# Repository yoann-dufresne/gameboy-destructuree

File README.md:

# Game Boy Pocket déstructurée

Un projet artistique : éclater une Game Boy Pocket en objets indépendants qui se parlent
par WiFi.

Chaque module est un projet à part entière : il a son matériel, son firmware, sa
documentation, et il sert à quelque chose en dehors de la Game Boy.

## Modules

| Module | Ce qu'il fait |
|---|---|
| [`capture/`](capture/) | Espionne le bus LCD d'une vraie Game Boy Pocket et diffuse son image en UDP, sans perturber la console. |
| [`ecran/`](ecran/) | Afficheur réseau sur matrices LED, 192×192 pixels visés. Il affiche toute image qu'on lui envoie en UDP, quelle qu'en soit la source. |
| [`son/`](son/) | Prend le son d'une Game Boy Pocket avant son bouton de volume et le diffuse en UDP ; un haut-parleur réseau le joue. Phase 0 prête : banc de mesure, plan, tests et points de prise. |
| [`manette/`](manette/) | Une seconde Game Boy Pocket devenue manette WiFi : ses boutons, ses molettes et son interrupteur partent en UDP vers la console principale, où un injecteur appuie sur les boutons et l'allume ou l'éteint. Plan écrit, rien de construit. |
| [`cartouche/`](cartouche/) | La cartouche dans une fente à part : un lecteur la lit à l'insertion et en envoie la copie en WiFi à une doublure branchée sur la console principale, qui tient le rôle de la cartouche. Les sauvegardes reviennent à la vraie cartouche. Plan écrit, rien de construit. |

Les modules ne partagent que des protocoles réseau sur UDP : `PXL1` pour l'image ; `SON1`
pour le son, `MAN1` pour la manette et `CAR1` pour la cartouche, proposés. Chacun s'éprouve
seul : `capture` avec un écran virtuel sur PC, `ecran` avec un émetteur de test, `son` avec un
haut-parleur virtuel et un émetteur de test, `manette` avec un récepteur et une fausse manette
sur PC, `cartouche` avec un PC qui lit le lecteur ou envoie une ROM à la doublure.

Sur la console, chaque module a son microcontrôleur, qui émet son propre réseau WiFi : jusqu'à
quatre écrans, haut-parleurs ou manettes s'y connectent en direct. Le plan d'ensemble est dans
[`reseau.md`](reseau.md).

## Installer les outils

[`installer.sh`](installer.sh) installe, sur Ubuntu ou Debian, ce que tous les modules demandent :
`arm-none-eabi-gcc`, CMake, Ninja, `g++` pour les tests sur PC, le pico-sdk 2.3.1 dans
`~/pico/pico-sdk`, picotool, les outils Python et `sigrok-cli`. Il se relance sans danger.

Sous WSL2, l'USB passe par `usbipd-win` côté Windows ; le script affiche à la fin les commandes
à y taper. Les `tools/flash.sh` des modules reconnaissent WSL2 : ils flashent par picotool si le
Pico est attaché à WSL, sinon par le lecteur `RP2350` que voit Windows.

## Documents de conception

| Document | Contenu |
|---|---|
| [`reseau.md`](reseau.md) | Le réseau : un réseau par type de périphérique, émis par la console ; canaux, adresses, bus de la console, banc de coexistence. |
| [`banc-reseau/`](banc-reseau/) | Le banc de coexistence de `reseau.md` : firmwares et outil de verdict pour éprouver les quatre radios de la console, le sniffer en point d'accès et le bus de la console. |
| [`achats.md`](achats.md) | La liste d'achats du 11/10/2026, tous modules confondus, pour leurs prochaines phases et le banc de coexistence. |
| [`Spec_Gameboy_Pocket_Destructuree.md`](Spec_Gameboy_Pocket_Destructuree.md) | L'intention : une vraie console au centre, cinq modules, et ce qui a changé depuis la v1, qui plaçait un émulateur dans la cartouche. |
| [`Spec_Video_Sniffer_et_Matrice_LED.md`](Spec_Video_Sniffer_et_Matrice_LED.md) | Le départ de la chaîne vidéo : l'image prise sur une vraie console plutôt que sur un émulateur. |

La spécification principale dit l'intention d'aujourd'hui ; la spécification vidéo est le
document de départ de la chaîne image. Là où elles divergent de la documentation d'un module,
c'est le module qui fait foi : ses mesures les ont corrigées.

## Licence

Sauf mention contraire, ce dépôt est distribué sous licence
[GNU Affero General Public License v3.0 ou ultérieure](LICENSE) (AGPL-3.0-or-later).

Le contenu tiers garde sa licence d'origine :

- `ecran/firmware/vendor/hub75-jupfu/` : pilote HUB75 de JuPfu, licence MIT.
- Les fichiers `pico_sdk_import.cmake`, `lwipopts.h` et `ecran/firmware/phase0-bringup/hub75.pio`,
  repris ou dérivés du pico-sdk et de pico-examples de Raspberry Pi : licence BSD-3-Clause.
- `ecran/docs/seengreat-rgb-matrix-p3-64x64/` : documentation et codes de démonstration du
  fabricant Seengreat, archivés pour référence ; ils restent la propriété de leurs auteurs.

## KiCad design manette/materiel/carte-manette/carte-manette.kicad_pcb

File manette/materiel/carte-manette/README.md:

# La carte de la manette : les fichiers

Le plan, les décisions et les étapes sont dans [`../../docs/carte.md`](../../docs/carte.md). Ici, la
carte elle-même, régénérée par script, comme [celle de l'écran](../../../ecran/materiel/README.md) :
on ne retouche pas les fichiers KiCad à la main. On modifie `conception.py` ou `gen_pcb.py`, puis on
relance `construire.sh`. Les fichiers restent ouvrables dans KiCad 10 pour les regarder.

**État au 15/11/2026.**
- **Schéma complet (C1)** : le contrôle électrique ne trouve aucune erreur ni aucun avertissement,
  et la netlist de KiCad est identique à `conception.py`.
- **Géométrie posée (C2)** : le contour, les trous et les 11 pièces reprises de YAPoco sont à leur
  place exacte. Le Pico et la LED d'alimentation sont posés.
- **Les autres pièces attendent leur placement (C4)**, rangées hors de la feuille. Il dépend des
  relevés des membranes (C0) et de l'essai en carton (C3).

| Fichier | Rôle |
|---|---|
| `conception.py` | la description électrique : composants, empreintes, équipotentielles, références d'achat. Source unique |
| `gen_schema.py` | écrit `carte-manette.kicad_sch`, sa bibliothèque de symboles et les tables du projet |
| `gen_pcb.py` | écrit `carte-manette.kicad_pcb` : contour, trous, pièces placées. Vérifie chaque pastille reprise de YAPoco |
| `extrait_yapoco.py` | a tiré de YAPoco le contour, les empreintes et leur place. N'a pas à être relancé |
| `yapoco/` | ce qui vient de YAPoco, et sa provenance |
| `carte-manette.pretty/` | les empreintes propres à la carte |
| `kicadlib.py`, `verifie_netlist.py`, `bilan_drc.py` | outils repris de la carte de l'écran, adaptés à KiCad 10 |
| `construire.sh` | tout, du schéma au gabarit |
| `gabarit/gabarit-echelle-1.pdf` | le gabarit de l'essai en carton (C3) : la face avant, puis le dos vu de dos |

```bash
cd manette/materiel/carte-manette
./construire.sh
```

Prérequis : KiCad 10 (`kicad-cli` et le module Python `pcbnew`), Python 3, `pdfunite`. Les tables
du projet ne listent que les bibliothèques de la carte ; celles de KiCad viennent de ses tables
globales, les tables par défaut proposées au premier lancement.

**Imprimer le gabarit à 100 %, sans ajustement à la page** : le contour doit mesurer 69,5 × 114,4 mm
sur le papier.

## Licence

La carte reprend la géométrie de [YAPoco](https://github.com/nataliethenerd/YAPoco), de Natalie the
Nerd, publiée sous [CC BY-SA 4.0](https://creativecommons.org/licenses/by-sa/4.0/). Ce dossier est
publié sous la même licence ; le détail de ce qui est repris est dans
[`yapoco/PROVENANCE.txt`](yapoco/PROVENANCE.txt).

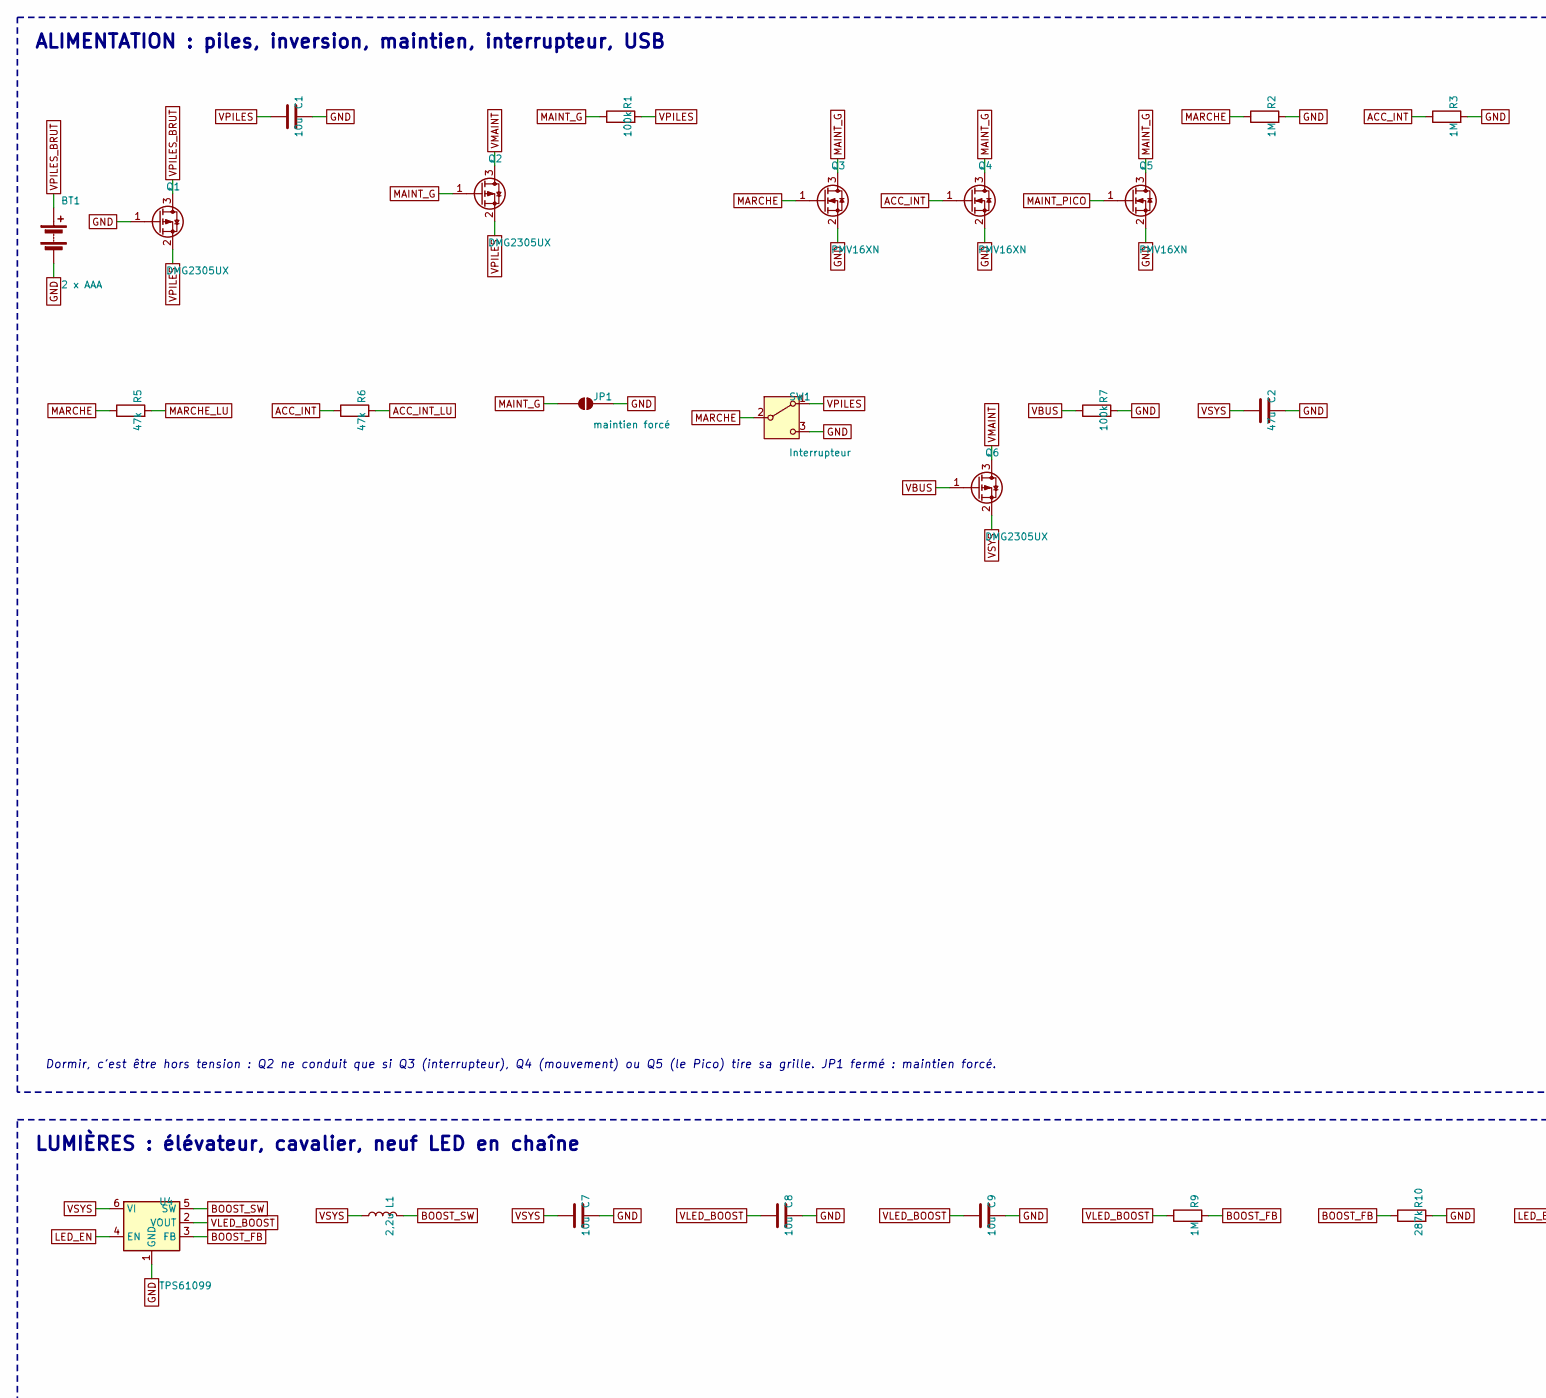
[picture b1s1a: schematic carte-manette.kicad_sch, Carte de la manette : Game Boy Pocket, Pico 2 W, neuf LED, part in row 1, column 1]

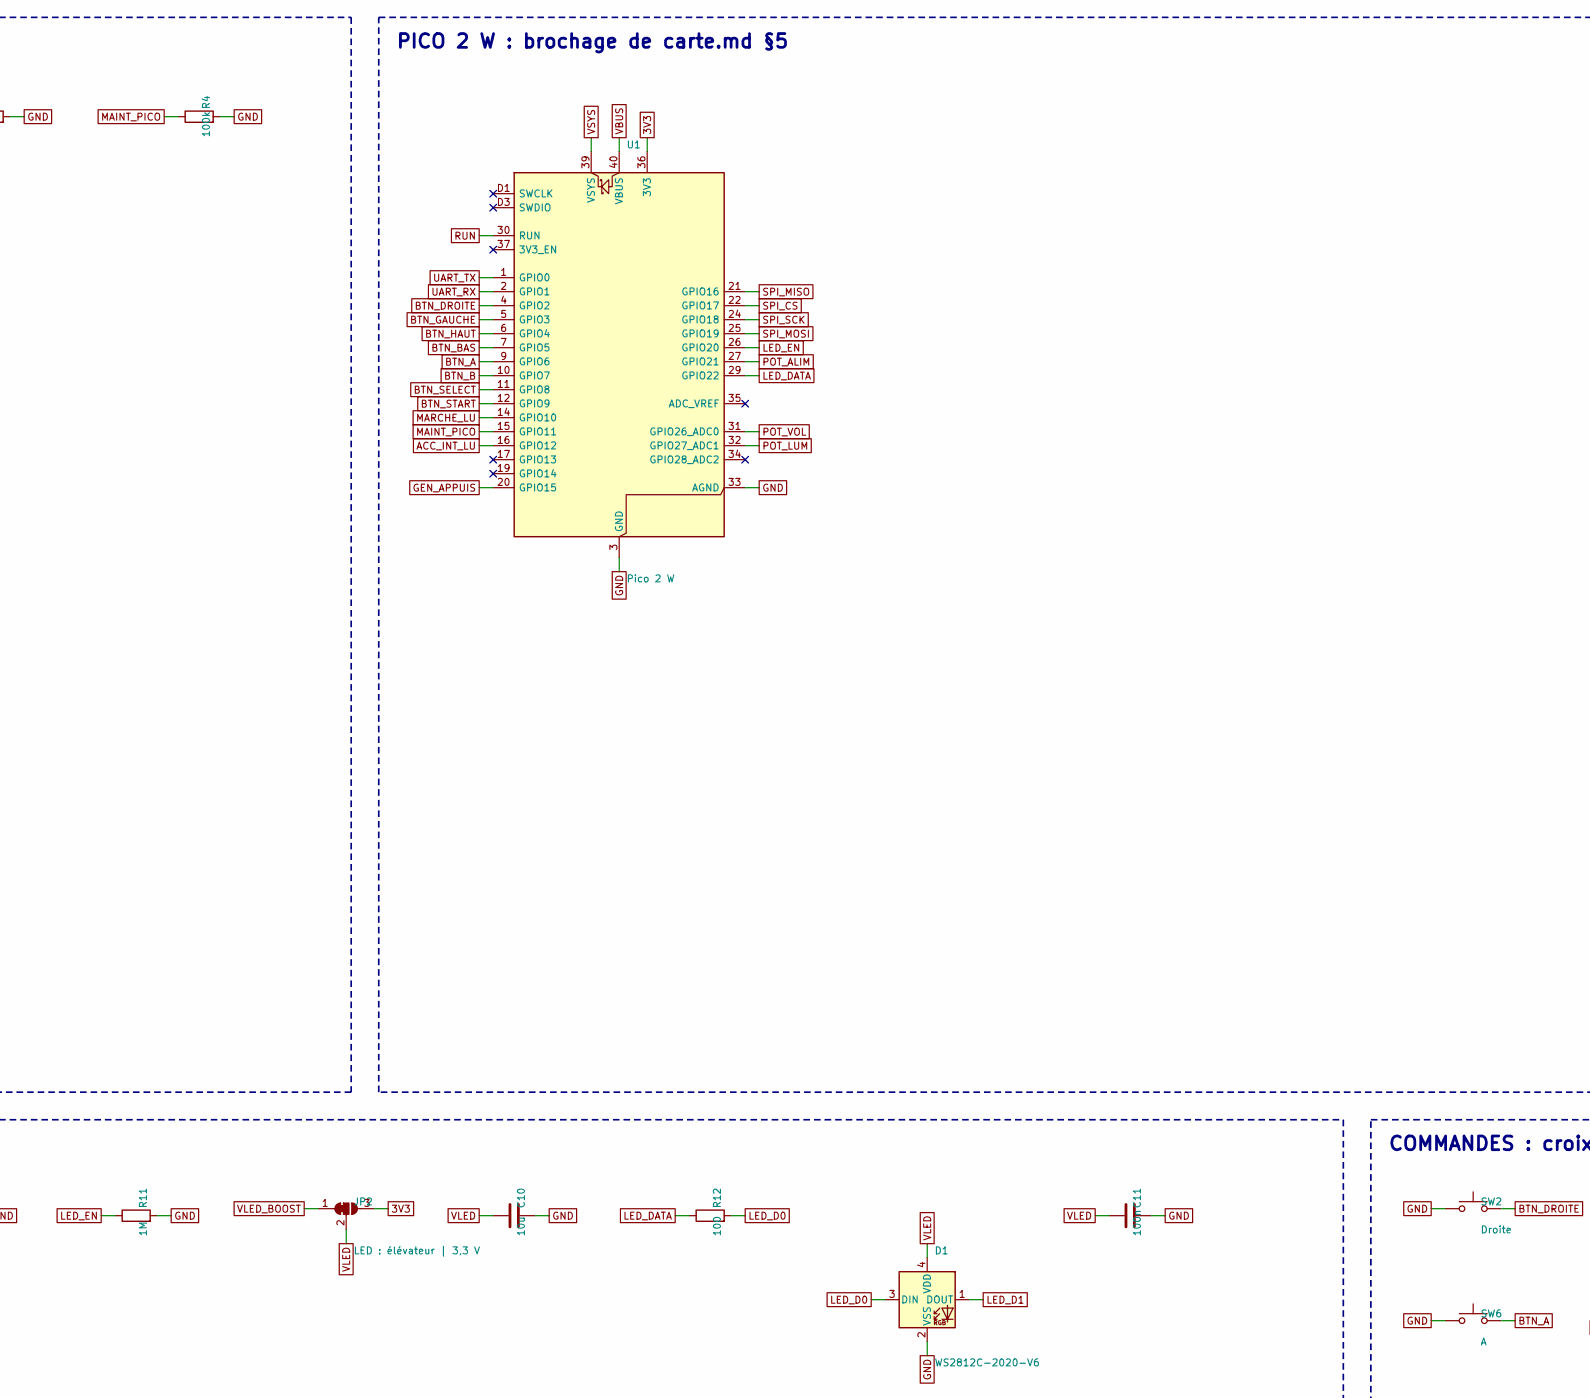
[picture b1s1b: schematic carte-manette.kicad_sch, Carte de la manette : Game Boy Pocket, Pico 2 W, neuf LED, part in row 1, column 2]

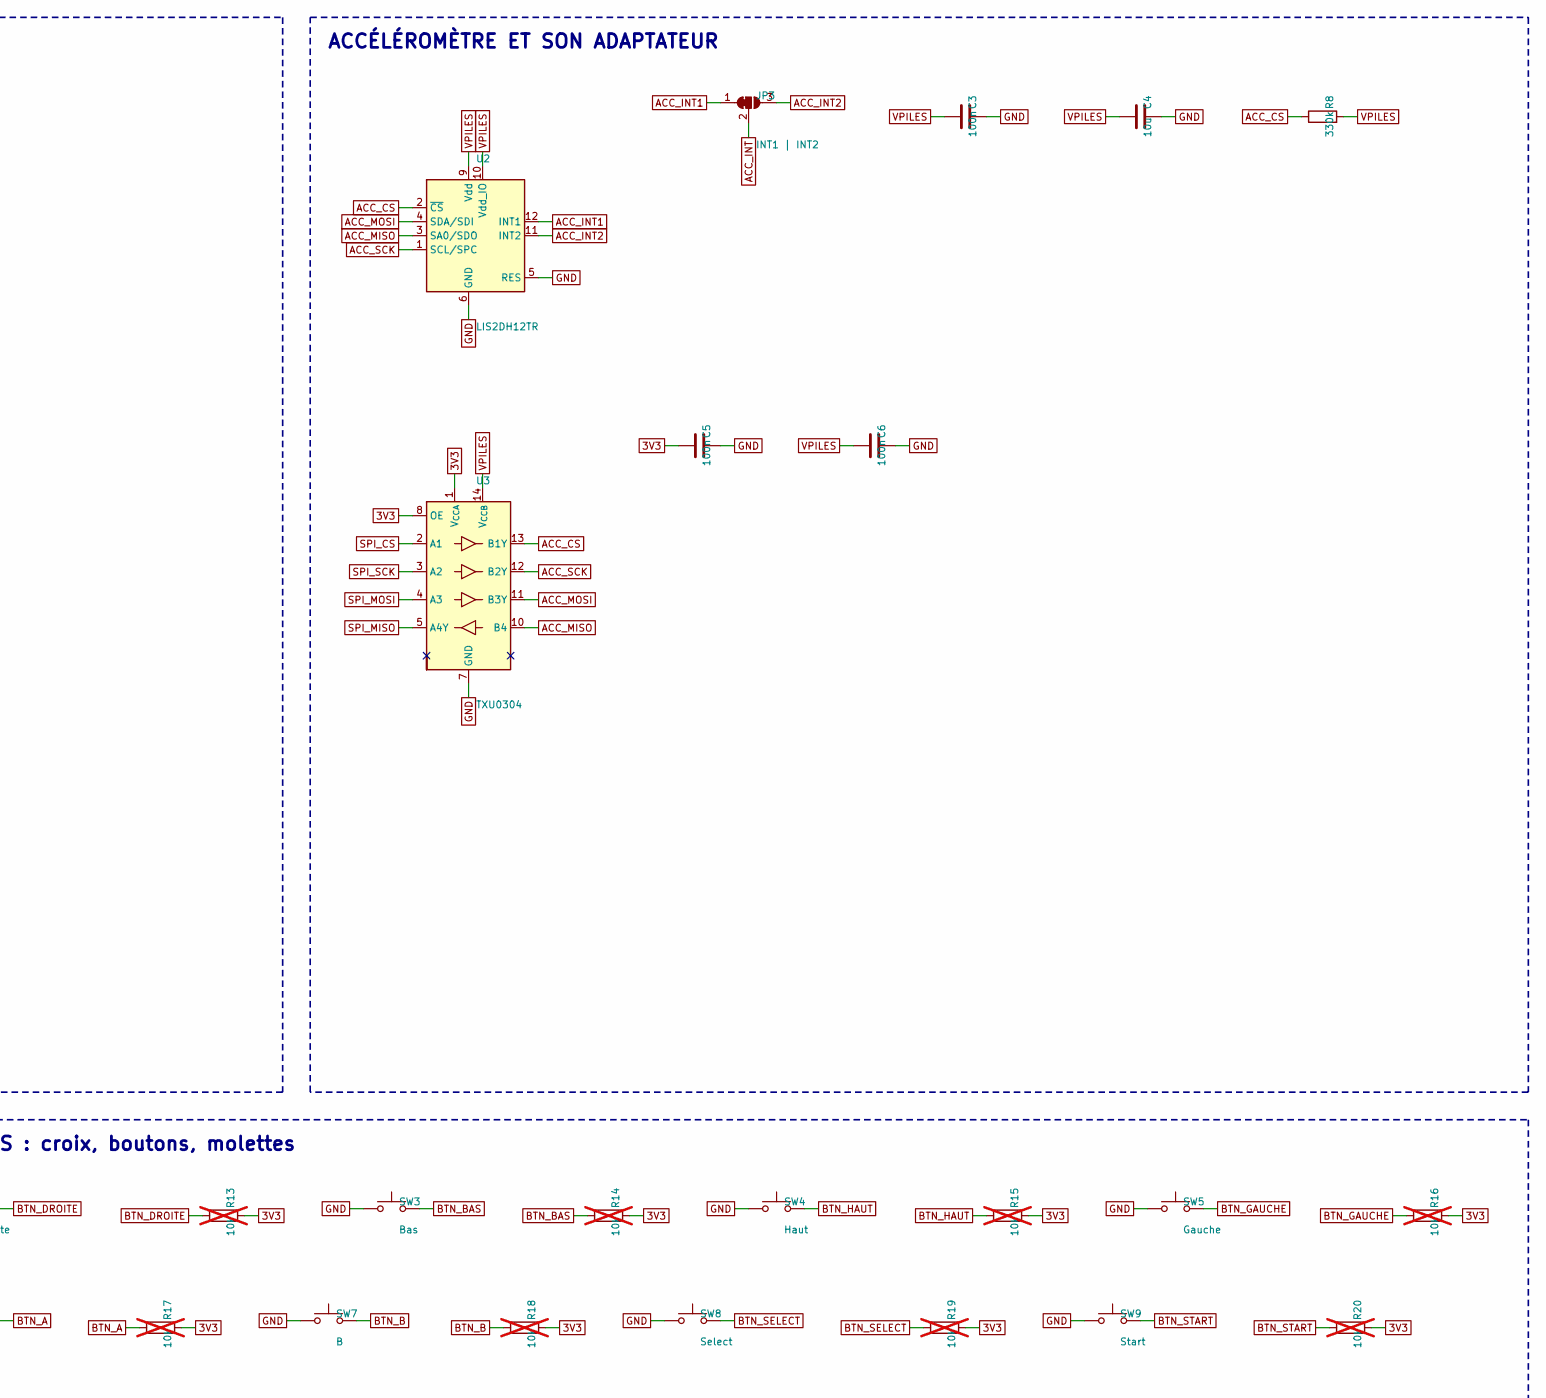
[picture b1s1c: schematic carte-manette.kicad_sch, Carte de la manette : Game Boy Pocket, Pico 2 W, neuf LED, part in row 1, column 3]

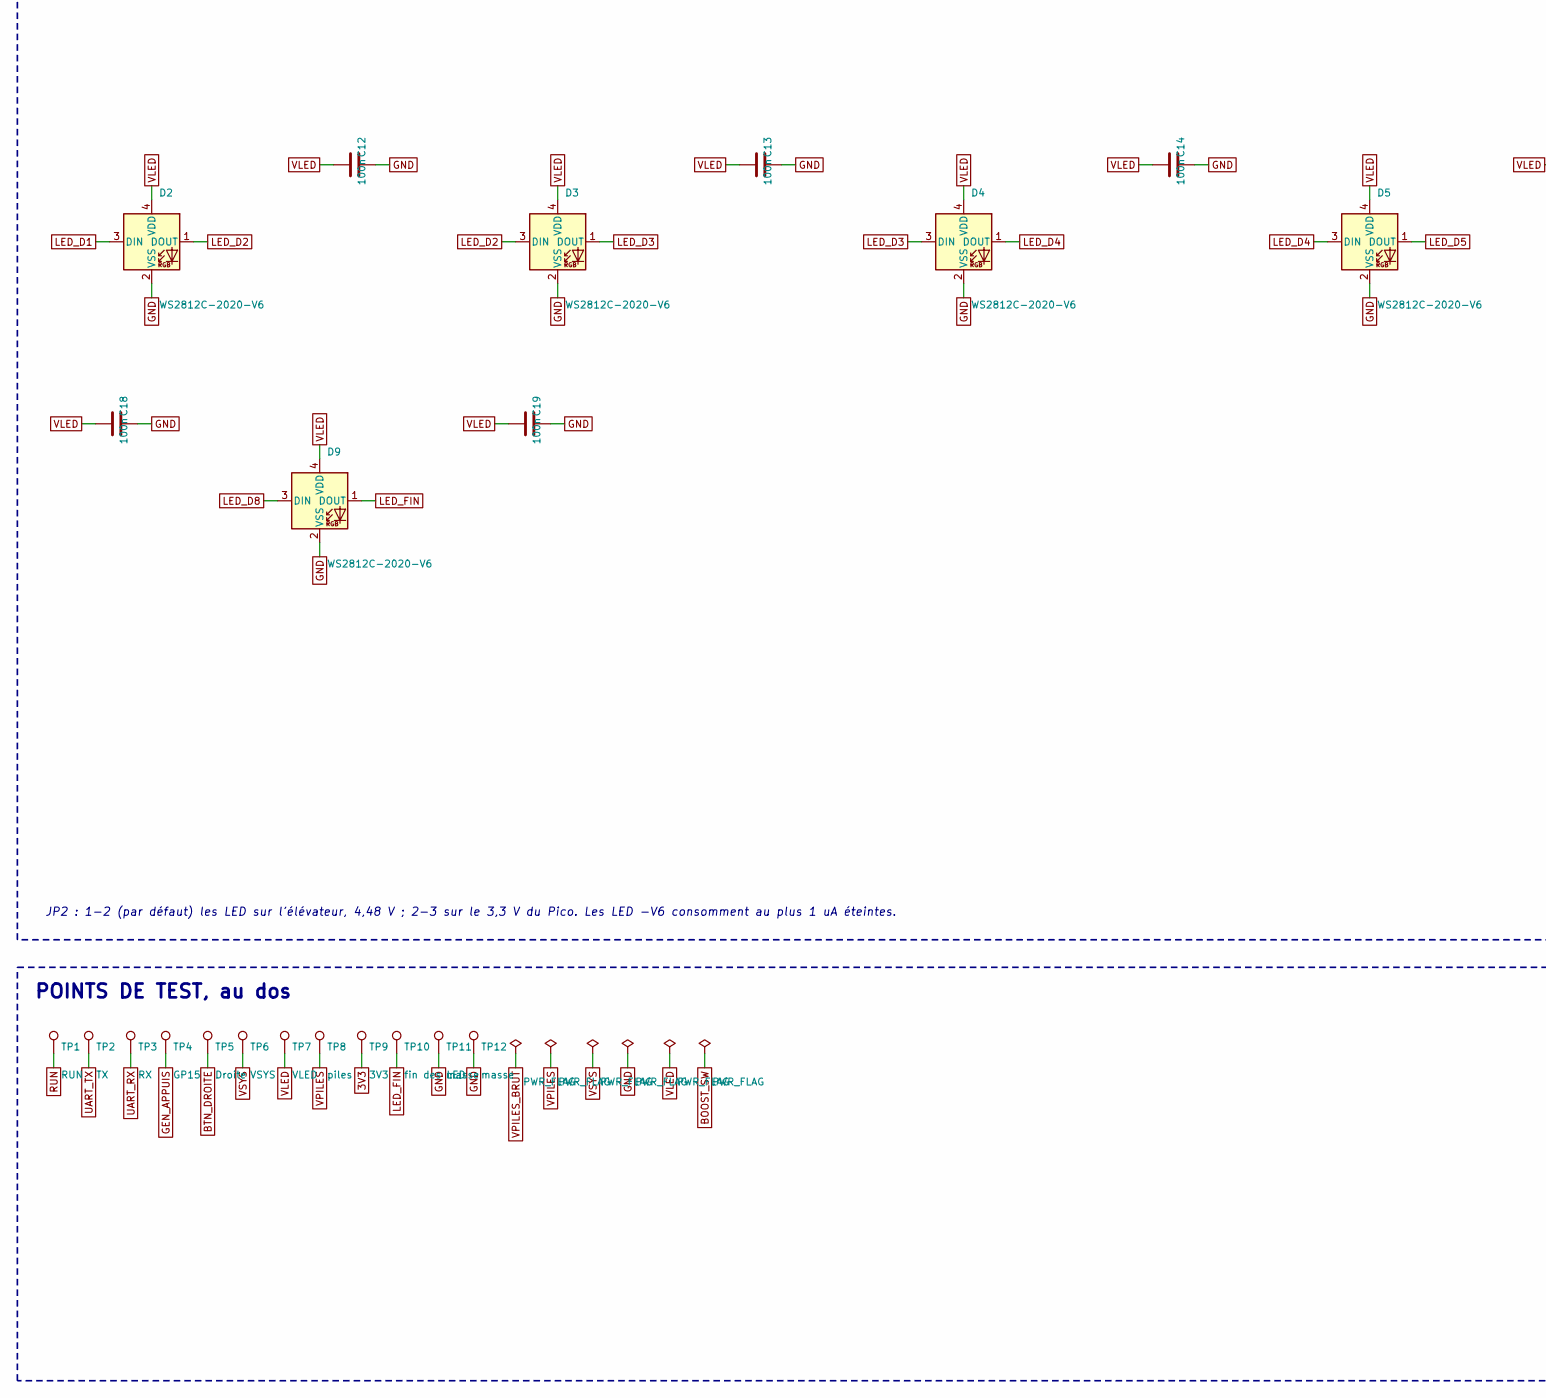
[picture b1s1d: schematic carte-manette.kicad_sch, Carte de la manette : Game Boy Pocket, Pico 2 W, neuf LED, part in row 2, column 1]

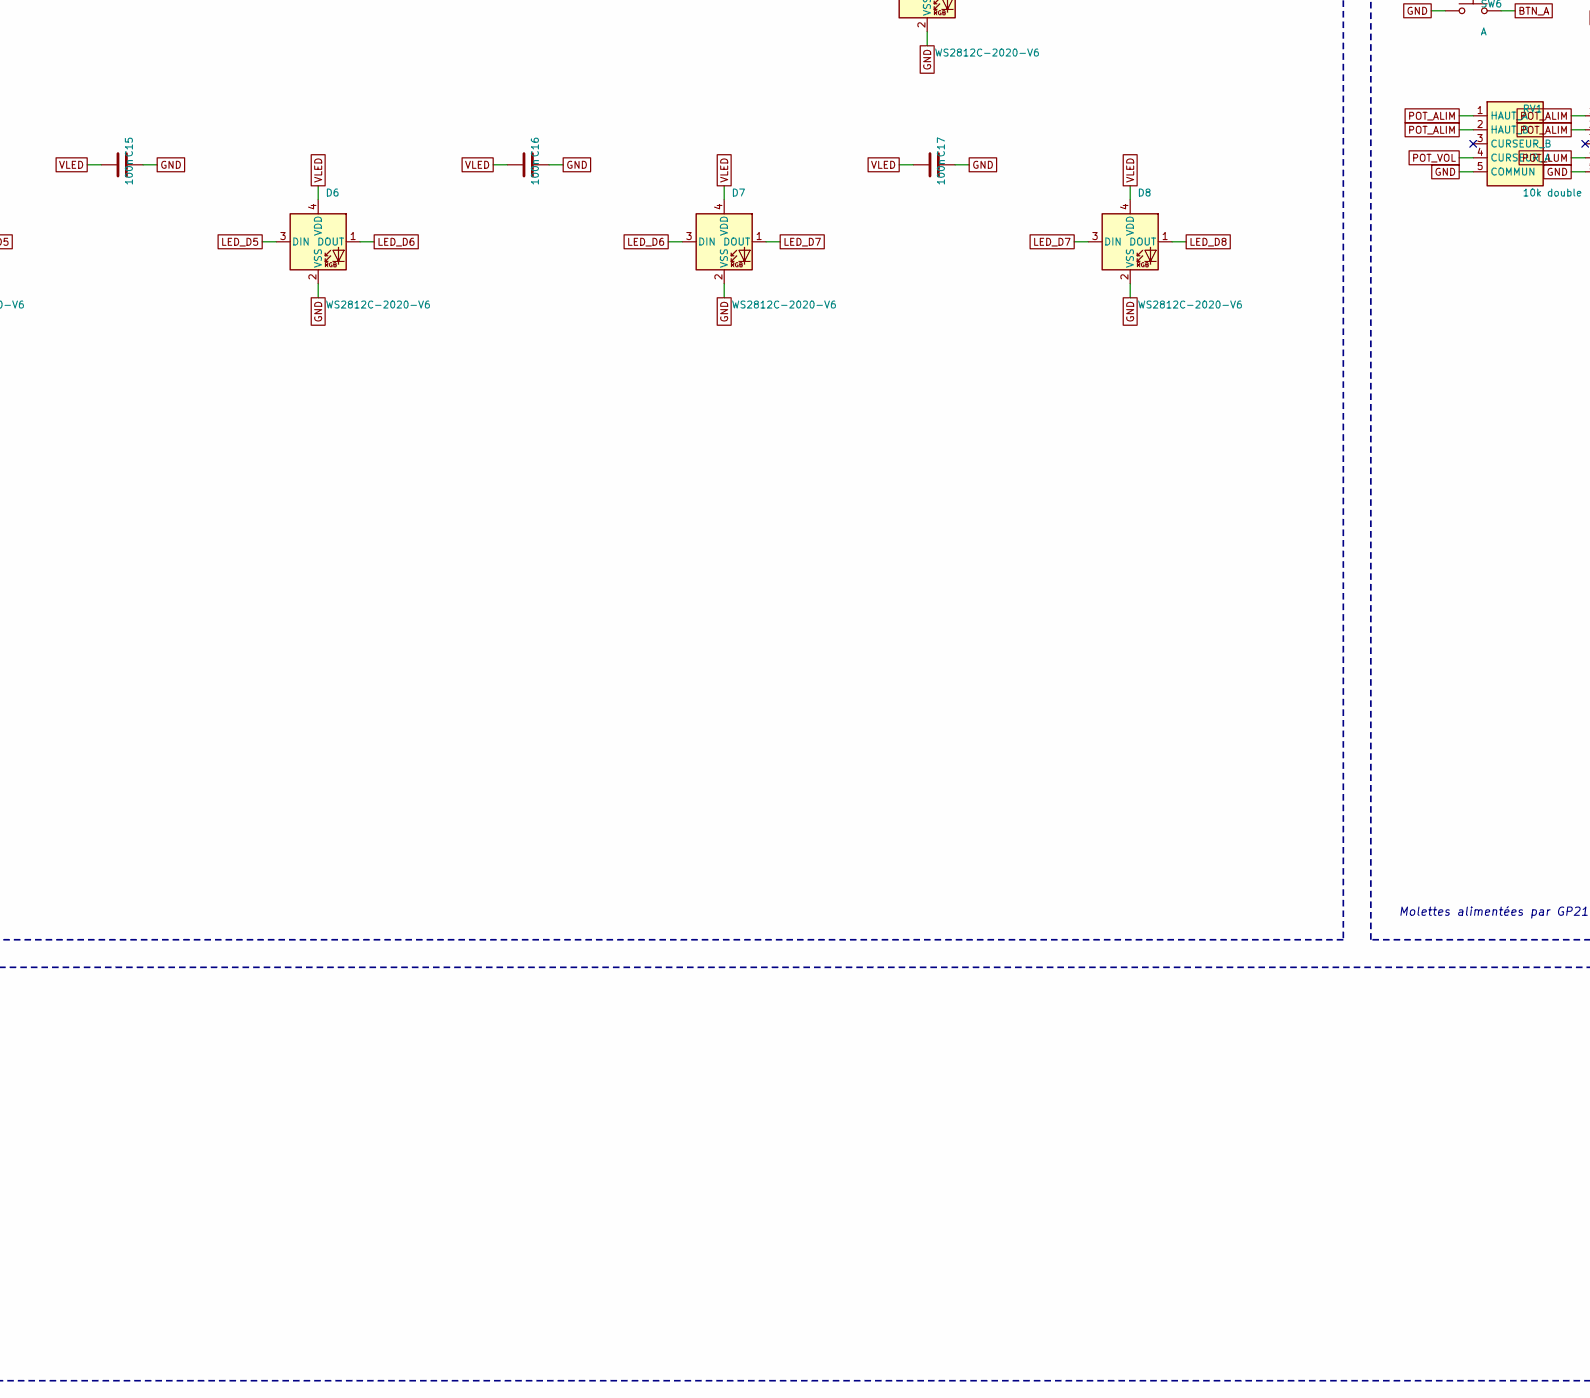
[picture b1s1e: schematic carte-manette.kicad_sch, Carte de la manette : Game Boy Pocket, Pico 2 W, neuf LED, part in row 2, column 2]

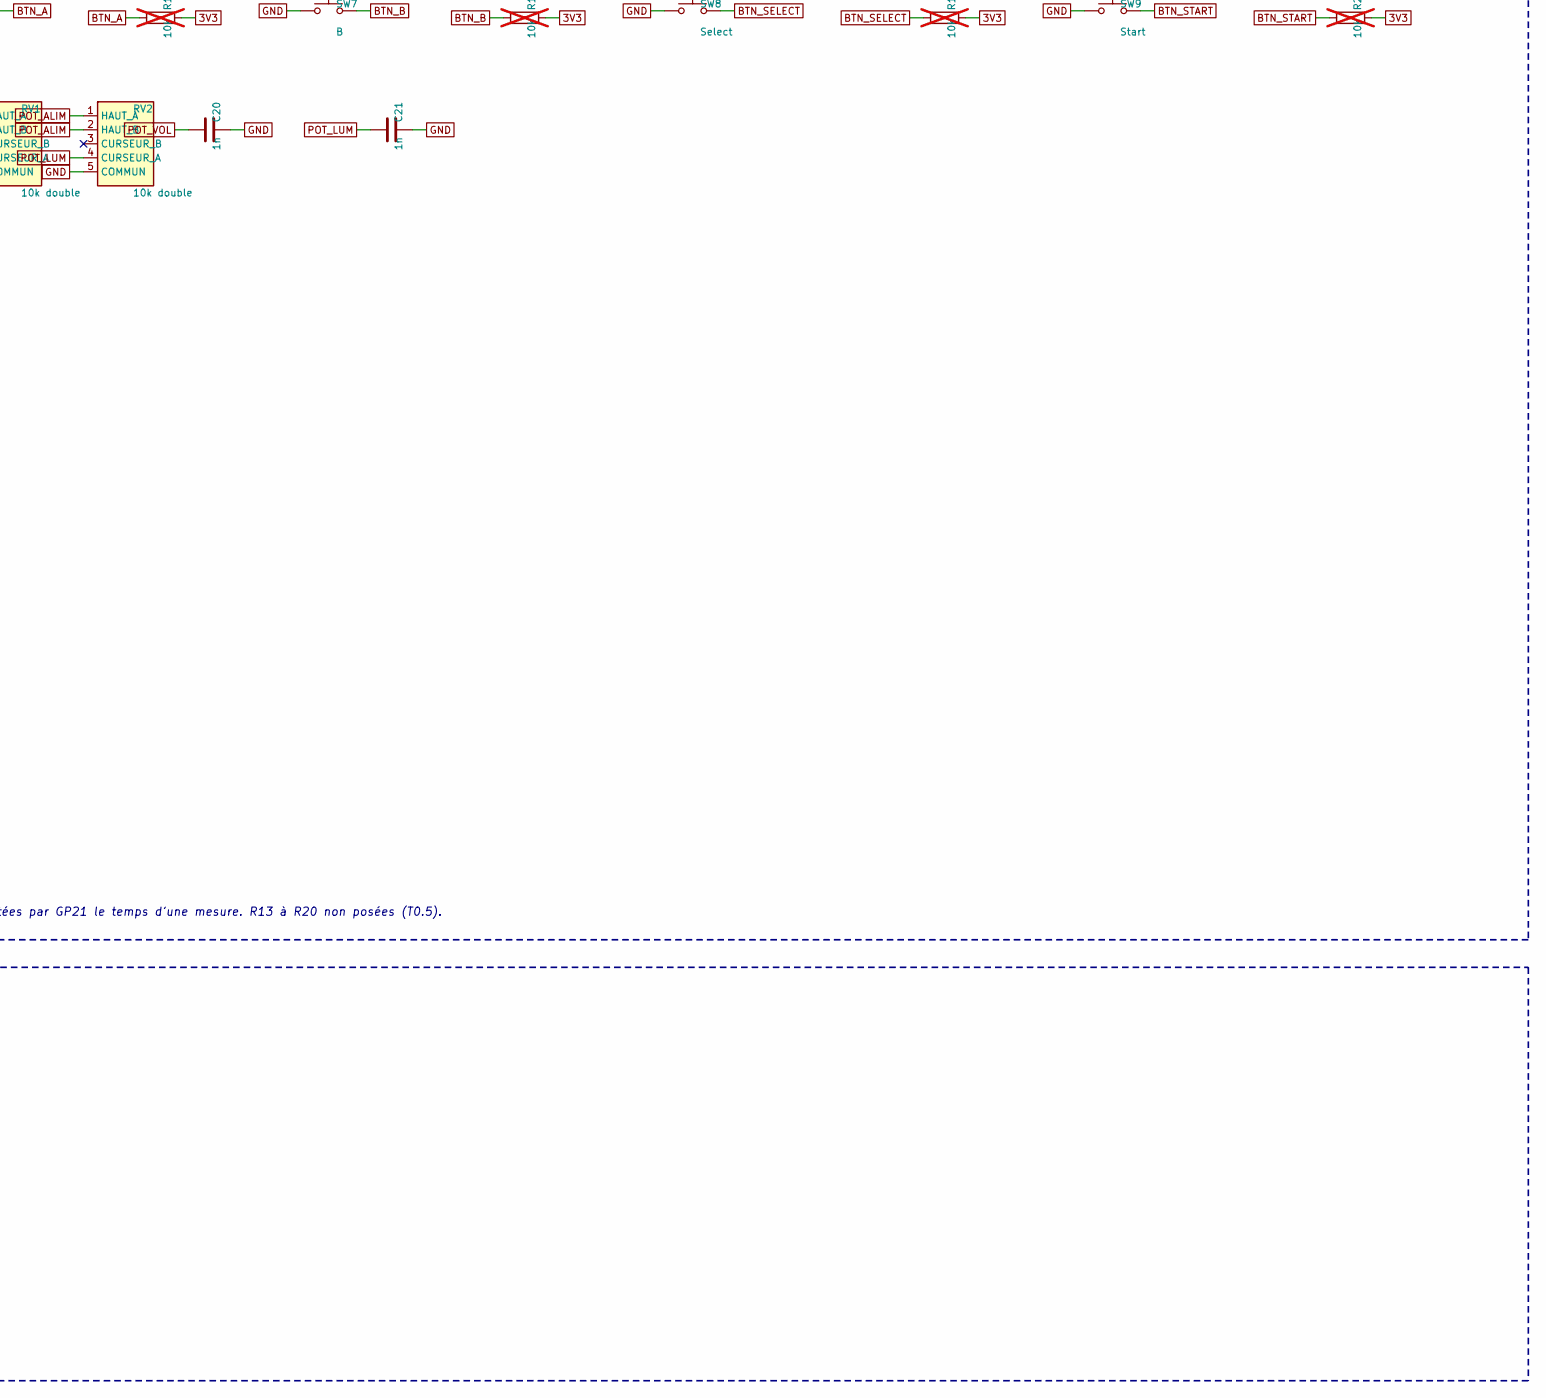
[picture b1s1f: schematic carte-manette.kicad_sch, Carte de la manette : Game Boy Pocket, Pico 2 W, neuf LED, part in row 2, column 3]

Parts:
BT1: 2 x AAA; YAPoco_Piles; MPN Contacts de piles de rechange Game Boy 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
C1, C4, C7, C8, C9, C10: 10u; C_0603_1608Metric; MPN 10 uF 10 V 0603 X5R
C2: 47u; C_1206_3216Metric; MPN 47 uF 6,3 V 1206 X5R
C3, C5, C6, C11, C12, C13, C14, C15, C16, C17, C18, C19: 100n; C_0603_1608Metric; MPN CC0603KRX7R9BB104; LCSC C14663
C20, C21: 1n; C_0603_1608Metric; MPN 1 nF 0603 X7R
D1, D2, D3, D4, D5, D6, D7, D8, D9: WS2812C-2020-V6; LED_WS2812B-2020_PLCC4_2.0x2.0mm; MPN WS2812C-2020-V6 (Worldsemi); LCSC C55109522
JP1: maintien forcé; SolderJumper-2_P1.3mm_Open_RoundedPad1.0x1.5mm
JP2: LED : élévateur | 3,3 V; SolderJumper-3_P1.3mm_Bridged12_RoundedPad1.0x1.5mm
JP3: INT1 | INT2; SolderJumper-3_P1.3mm_Bridged12_RoundedPad1.0x1.5mm
L1: 2,2u; L_1008_2520Metric; MPN 2,2 uH, 2520, saturation 1,5 A au moins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
PF1, PF2, PF3, PF4, PF5, PF6: PWR_FLAG
Q1, Q2, Q6: DMG2305UX; SOT-23; MPN DMG2305UX-7 (Diodes); LCSC C150470
Q3, Q4, Q5: PMV16XN; SOT-23; MPN PMV16XNR (Nexperia); LCSC C110920
R1, R4, R7: 100k; R_0603_1608Metric; MPN 100 kohm 0603
R2, R3, R9, R11: 1M; R_0603_1608Metric; MPN 1 Mohm 1 % 0603
R5, R6: 47k; R_0603_1608Metric; MPN 47 kohm 0603
R8: 330k; R_0603_1608Metric; MPN 330 kohm 0603
R10: 287k; R_0603_1608Metric; MPN 287 kohm 1 % 0603
R12: 100; R_0603_1608Metric; MPN 100 ohm 0603
R13, R14, R15, R16, R17, R18, R19, R20: 10k; R_0603_1608Metric; MPN 0603WAF1002T5E; LCSC C25804; not fitted
RV1, RV2: 10k double; YAPoco_Molette; MPN Potentiomètre 10 kohm GBC/GBP/GBA (Sile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
SW1: Interrupteur; YAPoco_Interrupteur; MPN Interrupteur de rechange Game Boy Pocke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
SW2: Droite; YAPoco_Croix; MPN Membranes RetroSix transparentes et bou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
SW3: Bas; YAPoco_Croix; MPN Membranes RetroSix transparentes et bou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
SW4: Haut; YAPoco_Croix; MPN Membranes RetroSix transparentes et bou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
SW5: Gauche; YAPoco_Croix; MPN Membranes RetroSix transparentes et bou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
SW6: A; YAPoco_AB; MPN Membranes RetroSix transparentes et bou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
SW7: B; YAPoco_AB; MPN Membranes RetroSix transparentes et bou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
SW8: Select; YAPoco_Select; MPN Membranes RetroSix transparentes et bou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
SW9: Start; YAPoco_Start; MPN Membranes RetroSix transparentes et bou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
TP1: RUN; TestPoint_Pad_D1.0mm
TP2: TX; TestPoint_Pad_D1.0mm
TP3: RX; TestPoint_Pad_D1.0mm
TP4: GP15; TestPoint_Pad_D1.0mm
TP5: Droite; TestPoint_Pad_D1.0mm
TP6: VSYS; TestPoint_Pad_D1.0mm
TP7: VLED; TestPoint_Pad_D1.0mm
TP8: piles; TestPoint_Pad_D1.0mm
TP9: 3V3; TestPoint_Pad_D1.0mm
TP10: fin des LED; TestPoint_Pad_D1.0mm
TP11, TP12: masse; TestPoint_Pad_D1.0mm
U1: Pico 2 W; RaspberryPi_Pico_W_SMD_HandSolder; MPN Raspberry Pi Pico 2 W, soudé à plat à l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
U2: LIS2DH12TR; LGA-12_2x2mm_P0.5mm; MPN LIS2DH12TR (ST); LCSC C110926
U3: TXU0304; TSSOP-14_4.4x5mm_P0.65mm; MPN TXU0304PWR (TI); LCSC C4364118
U4: TPS61099; WSON-6-1EP_2x2mm_P0.65mm_EP1x1.6mm; MPN TPS61099DRVR (TI); LCSC C2842395

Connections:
3V3: C5.1, JP2.3 (B), R13.2, R14.2, R15.2, R16.2, R17.2, R18.2, R19.2, R20.2, TP9.1, U1.36 (3V3), U3.1 (V_{CCA}), U3.8 (OE)
ACC_CS: R8.1, U2.2 (~CS), U3.13 (B1Y)
ACC_INT: JP3.2 (C), Q4.1 (G), R3.1, R6.1
ACC_INT1: JP3.1 (A), U2.12 (INT1)
ACC_INT2: JP3.3 (B), U2.11 (INT2)
ACC_INT_LU: R6.2, U1.16 (GPIO12)
ACC_MISO: U2.3 (SA0/SDO), U3.10 (B4)
ACC_MOSI: U2.4 (SDA/SDI), U3.11 (B3Y)
ACC_SCK: U2.1 (SCL/SPC), U3.12 (B2Y)
BOOST_FB: R9.2, R10.1, U4.3 (FB)
BOOST_SW: L1.2, PF6.1, U4.5 (SW)
BTN_A: R17.1, SW6.2, U1.9 (GPIO6)
BTN_B: R18.1, SW7.2, U1.10 (GPIO7)
BTN_BAS: R14.1, SW3.2, U1.7 (GPIO5)
BTN_DROITE: R13.1, SW2.2, TP5.1, U1.4 (GPIO2)
BTN_GAUCHE: R16.1, SW5.2, U1.5 (GPIO3)
BTN_HAUT: R15.1, SW4.2, U1.6 (GPIO4)
BTN_SELECT: R19.1, SW8.2, U1.11 (GPIO8)
BTN_START: R20.1, SW9.2, U1.12 (GPIO9)
GEN_APPUIS: TP4.1, U1.20 (GPIO15)
GND: BT1.2 (-), C1.2, C2.2, C3.2, C4.2, C5.2, C6.2, C7.2, C8.2, C9.2, C10.2, C11.2, C12.2, C13.2, C14.2, C15.2, C16.2, C17.2, C18.2, C19.2, C20.2, C21.2, D1.2 (VSS), D2.2 (VSS), D3.2 (VSS), D4.2 (VSS), D5.2 (VSS), D6.2 (VSS), D7.2 (VSS), D8.2 (VSS), D9.2 (VSS), JP1.2 (B), PF4.1, Q1.1 (G), Q3.2 (S), Q4.2 (S), Q5.2 (S), R2.2, R3.2, R4.2, R7.2, R10.2, R11.2, RV1.5 (COMMUN), RV2.5 (COMMUN), SW1.3 (C), SW2.1, SW3.1, SW4.1, SW5.1, SW6.1, SW7.1, SW8.1, SW9.1, TP11.1, TP12.1, U1.3 (GND), U1.8 (GND), U1.13 (GND), U1.18 (GND), U1.23 (GND), U1.28 (GND), U1.33 (AGND), U1.38 (GND), U1.D2 (GND), U2.5 (RES), U2.6 (GND), U2.7 (GND), U2.8 (GND), U3.7 (GND), U4.1 (GND), U4.7 (GND)
LED_D0: D1.3 (DIN), R12.2
LED_D1: D1.1 (DOUT), D2.3 (DIN)
LED_D2: D2.1 (DOUT), D3.3 (DIN)
LED_D3: D3.1 (DOUT), D4.3 (DIN)
LED_D4: D4.1 (DOUT), D5.3 (DIN)
LED_D5: D5.1 (DOUT), D6.3 (DIN)
LED_D6: D6.1 (DOUT), D7.3 (DIN)
LED_D7: D7.1 (DOUT), D8.3 (DIN)
LED_D8: D8.1 (DOUT), D9.3 (DIN)
LED_DATA: R12.1, U1.29 (GPIO22)
LED_EN: R11.1, U1.26 (GPIO20), U4.4 (EN)
LED_FIN: D9.1 (DOUT), TP10.1
MAINT_G: JP1.1 (A), Q2.1 (G), Q3.3 (D), Q4.3 (D), Q5.3 (D), R1.1
MAINT_PICO: Q5.1 (G), R4.1, U1.15 (GPIO11)
MARCHE: Q3.1 (G), R2.1, R5.1, SW1.2 (B)
MARCHE_LU: R5.2, U1.14 (GPIO10)
POT_ALIM: RV1.1 (HAUT_A), RV1.2 (HAUT_B), RV2.1 (HAUT_A), RV2.2 (HAUT_B), U1.27 (GPIO21)
POT_LUM: C21.1, RV2.4 (CURSEUR_A), U1.32 (GPIO27_ADC1)
POT_VOL: C20.1, RV1.4 (CURSEUR_A), U1.31 (GPIO26_ADC0)
RUN: TP1.1, U1.30 (RUN)
SPI_CS: U1.22 (GPIO17), U3.2 (A1)
SPI_MISO: U1.21 (GPIO16), U3.5 (A4Y)
SPI_MOSI: U1.25 (GPIO19), U3.4 (A3)
SPI_SCK: U1.24 (GPIO18), U3.3 (A2)
UART_RX: TP3.1, U1.2 (GPIO1)
UART_TX: TP2.1, U1.1 (GPIO0)
VBUS: Q6.1 (G), R7.1, U1.40 (VBUS)
VLED: C10.1, C11.1, C12.1, C13.1, C14.1, C15.1, C16.1, C17.1, C18.1, C19.1, D1.4 (VDD), D2.4 (VDD), D3.4 (VDD), D4.4 (VDD), D5.4 (VDD), D6.4 (VDD), D7.4 (VDD), D8.4 (VDD), D9.4 (VDD), JP2.2 (C), PF5.1, TP7.1
VLED_BOOST: C8.1, C9.1, JP2.1 (A), R9.1, U4.2 (VOUT)
VMAINT: Q2.3 (D), Q6.3 (D)
VPILES: C1.1, C3.1, C4.1, C6.1, PF2.1, Q1.2 (S), Q2.2 (S), R1.2, R8.2, SW1.1 (A), TP8.1, U2.9 (Vdd), U2.10 (Vdd_IO), U3.14 (V_{CCB})
VPILES_BRUT: BT1.1 (+), PF1.1, Q1.3 (D)
VSYS: C2.1, C7.1, L1.1, PF3.1, Q6.2 (S), TP6.1, U1.39 (VSYS), U4.6 (VI)

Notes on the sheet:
ALIMENTATION : piles, inversion, maintien, interrupteur, USB
PICO 2 W : brochage de carte.md §5
ACCÉLÉROMÈTRE ET SON ADAPTATEUR
LUMIÈRES : élévateur, cavalier, neuf LED en chaîne
COMMANDES : croix, boutons, molettes
POINTS DE TEST, au dos
Dormir, c'est être hors tension : Q2 ne conduit que si Q3 (interrupteur), Q4 (mouvement) ou Q5 (le Pico) tire sa grille. JP1 fermé : maintien forcé.
JP2 : 1-2 (par défaut) les LED sur l'élévateur, 4,48 V ; 2-3 sur le 3,3 V du Pico. Les LED -V6 consomment au plus 1 uA éteintes.
Molettes alimentées par GP21 le temps d'une mesure. R13 à R20 non posées (T0.5).

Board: 2 copper layers, 88 parts (3 on the bottom side), 54 nets, no tracks yet.

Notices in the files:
manette/materiel/carte-manette/carte-manette.kicad_pcb:
CC BY-SA 4.0 - geometrie : YAPoco, Natalie the Nerd
manette/materiel/carte-manette/carte-manette.kicad_sch:
Licence CC BY-SA 4.0 : géométrie reprise de YAPoco, de Natalie the Nerd
parts and their libraries:
YAPoco (Natalie the Nerd), CC BY-SA 4.0, https://github.com/nataliethenerd/YAPoco, empreinte \"Select CGB\"
YAPoco (Natalie the Nerd), CC BY-SA 4.0, https://github.com/nataliethenerd/YAPoco, empreinte \"AB CGB\"
